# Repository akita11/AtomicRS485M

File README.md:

# Atomic RS485M Base

RS485規格の半二重シリアル通信を行うことができるAtomic Baseです。
M5StackのATOMシリーズを載せて使用します。

[M5Stack社のATOMIC RS485ベース](https://www.switch-science.com/products/9180)とは異なり、本来のRS485の通信仕様でマルチドロップの1:N通信トポロジを構成できます（詳細は後述）。
データを送信している期間のみ伝送路を送信駆動する制御を行うことができます（通信速度は変更可能）。

また伝送路側から最大24Vを供給してマイコン側に5Vを供給することができます。

理論上最大256台まで接続可能な低入力容量型のRS485ドライバを使用しています。

## RS485通信の基本構成と「M5Stack社のATOMIC RS485ベース」との相違点

RS485は、2本の伝送路(Line)を使ってシリアルデータ(UART)を送受信する規格です。
規格の詳細と、M5Stack社のATOMIC RS485ベースでの留意すべき点は[こちら](https://note.com/akita11/n/n0c082069f98c)を参照してください。

「M5Stack社のATOMIC RS485ベース」との相違点は以下です。
（以下のカッコ内の※以下は「M5Stack社のATOMIC RS485ベース」の仕様）

- 非送信時には伝送路が非駆動（※"1"で駆動）
- 送信時のみ伝送路を駆動、1バイト単位自動またはGPIOで制御、自動制御にも設定可能（※常時"1"で駆動）
- 給電入力は48Vまで、24V給電時の過渡応答でも破損しにくい（※給電入力の絶対最大定格が30Vのため24V給電時の過渡応答で破損する場合がある）

## 使い方

基本的には[M5Stack社のATOMIC RS485ベース](https://www.switch-science.com/products/9180)と同じ使い方ですが、送信制御のみ異なり、以下の通りの仕様です。

なおJP5をショートすると伝送路の終端抵抗（120Ω）をONにできます。
またJP6とJP7をショートすると、伝送路のプルアップ・プルダウンを有効にできます（Aプルアップ、Bがプルダウン（5.1kΩ））。

### データ送信

初期設定時には、TXen（ATOM Lite/Matrixの場合はGPIO23）でDriverの有効／無効を制御できます。

1:1接続時の単方向（1つが送信専用、もう1つが受信専用）の場合の送信側は、常時有効（TXen=1）でOKです。

1:N接続時（複数の回路が伝送路Lineにつながる）は、送信デバイスのみがTXen=1としてデータを送信し、その他のデバイスはTXen=0ととすることで、半二重通信が実現されます。

伝送路Receiverは、TXen=1（送信時）のみ無効となりますが、JP8を2-3側に切り替えると、伝送路レシーバReceiverを常時有効に設定できますが、この場合は、自分のDriverが送信したデータを常時受信することになります。

### 伝送路ドライバの自動制御

JP4をショートすると、Driverの自動制御が有効となります。
※このときATOM側のTXen（ATOM Lite/Matrixの場合はGPIO23）は入力設定としてください。

スタートビット検出から1バイト分（10bit分=STARTビット+データ8ビット+STOPビット）の時間だけ自動的にDriverが有効となり、伝送路にデータを送信します（伝送路を駆動中はLEDが点灯）。
このとき、Receiverは無効となり、データを受信しません。
通信方式はN81（8ビット・STOPビット1ビット、パリティなし）で固定です。

データ送信時にDriverを有効とする時間は、データ転送速度（ボーレート）に依存するため、後述の方法で変更できます

### 伝送速度（ボーレート）の変更

ATOM側からBREAK信号（一定時間以上、データ線を"L"に保持）することで、伝送速度変更モードに入り、LEDが点滅します。
この状態で、設定したい伝送速度（ボーレート）で以下のいずれか1バイトを送信することで、その波形から伝送速度を検出し、伝送速度の設定（Driverを有効とする時間）を変更します。
設定された伝送速度は電源を切っても保存されます。

- 'U' (0x55) : 1バイト伝送モード。1バイト伝送終了後の伝送路ドライバがDisableに戻ります。（LEDが3回点滅）
- '5' (0x35) : 連続伝送モード。送信開始語、一定時間データが送られなかった場合に伝送路ドライバがDisableに戻ります。（LEDが5回点滅）

なおBREAK信号は、ATOM等で生成、またはATOM等経由でPC用ターミナルソフトでも送出ができます（TeraTermではAlt+B、MacのscreenコマンドではCtrl+A→Ctr+B）。
[Groveケーブル-USBシリアル接続ケーブル](https://www.switch-science.com/products/9460)などを使って、PCと接続して設定変更や送受信テストができます。

### 電源給電の設定

デフォルトでは、外部からの12/24V給電から本体とATOMへ5Vを供給します。
JP1とJP9で給電方法を変更できます。

- JP9: 給電方法
  - 1-2間: 外部12/24Vから5Vを生成し、本体とATOMへ供給（デフォルト）
  - 2-3間: 外部給電をそのまま本体・ATOMへ接続（※この場合は外部からの給電電圧は5Vとしてください。5V以上の電圧を加えると破損する場合があります）

- JP1: RS485ドライバの電源電圧の変更
  - 1-2間=3.3V（デフォルト）
  - 2-3間=5V

## Author

Junichi Akita (@akita11) / akita@ifdl.jp

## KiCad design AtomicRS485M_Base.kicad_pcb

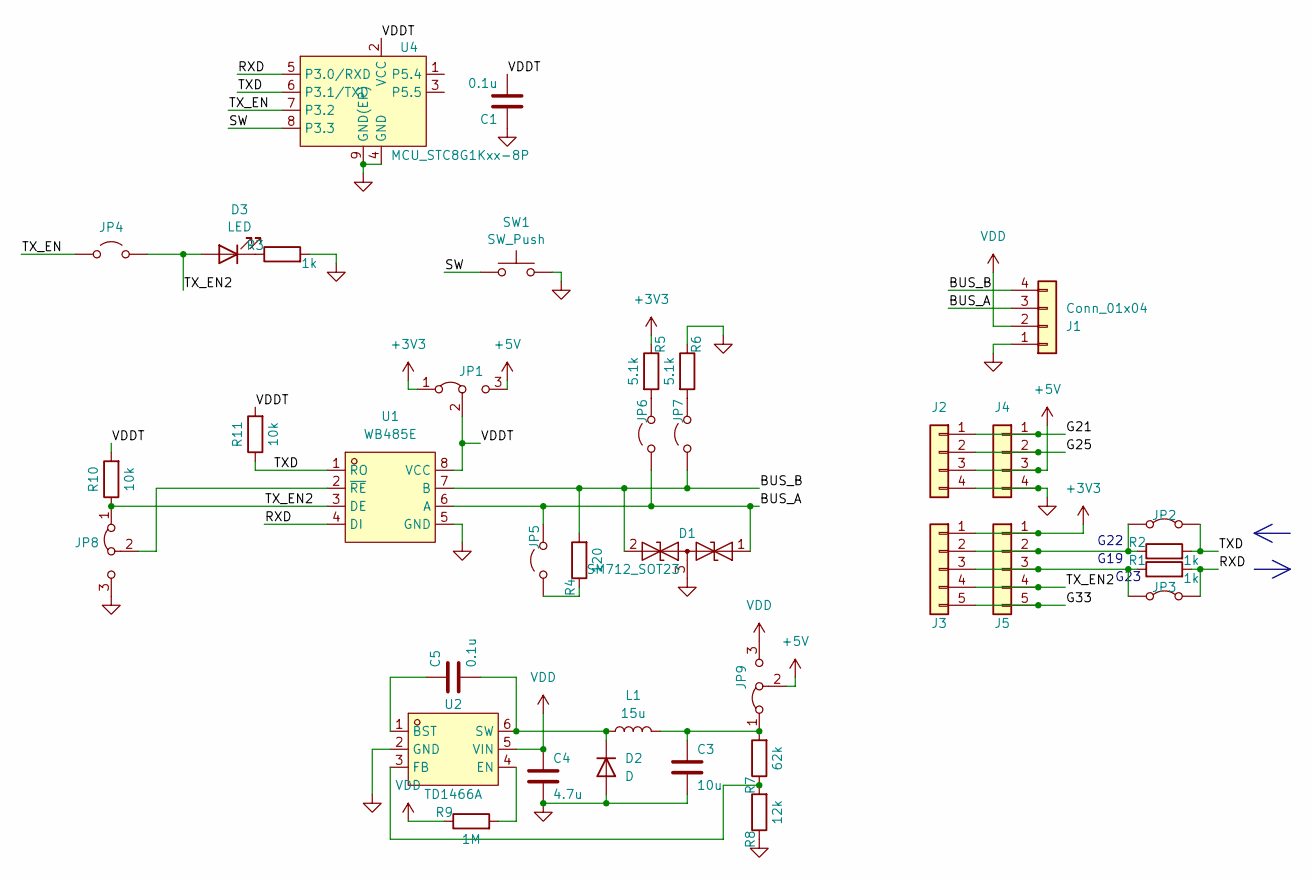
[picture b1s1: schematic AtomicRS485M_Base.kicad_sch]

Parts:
C1, C5: 0.1u; C_0603_1608Metric; LCSC Part C14663
C3: 10u; C_0603_1608Metric; LCSC Part C19702
C4: 4.7u; C_0603_1608Metric; LCSC Part C167655
D1: SM712_SOT23; SOT-23; LCSC Part C5180237
D2: D; D_SOD-123F; LCSC Part C190475
D3: LED; LED_0603_1608Metric; LCSC Part C2286
J1: Conn_01x04; CON_HT396R_4P_hole0.8sq
J2, J4: Conn_01x04; PinHeader_1x04_P2.54mm_Vertical
J3, J5: Conn_01x05; PinHeader_1x05_P2.54mm_Vertical
JP1, JP9: Jumper_3_Bridged12; SolderJumper-3_P1.3mm_Bridged2Bar12_Pad1.0x1.5mm
JP2, JP3: Jumper_2_Bridged; SolderJumper-2_P1.3mm_Bridged_Pad1.0x1.5mm
JP4, JP5, JP6, JP7: Jumper_2_Open; SolderJumper-2_P1.3mm_Open_Pad1.0x1.5mm
JP8: Jumper_3_Bridged12; SolderJumper-3_P1.3mm_Bridged12_Pad1.0x1.5mm
L1: 15u; L_CD43; LCSC Part C5289403
R1, R2, R3: 1k; R_0603_1608Metric; LCSC Part C21190
R4: 120; R_0603_1608Metric; LCSC Part C286567
R5, R6: 5.1k; R_0603_1608Metric; LCSC Part C23186
R7: 62k; R_0603_1608Metric; LCSC Part C3017756
R8: 12k; R_0603_1608Metric; LCSC Part C3017713
R9: 1M; R_0603_1608Metric; LCSC Part C2907115
R10, R11: 10k; R_0603_1608Metric; LCSC C25804
SW1: SW_Push; SW_Push_SPST_NO_Alps_SKRK
U1: WB485E; SOIC-8_L5.0-W4.0-P1.27-LS6.0-BL; LCSC Part C42460582
U2: TD1466A; SOT-23-6_L2.9-W1.7-P0.95-LS2.8-BL; LCSC Part C51928156
U4: MCU_STC8G1Kxx-8P; DFN-8-1EP_3x3mm_P0.5mm_EP1.65x2.38mm; LCSC Part C915664

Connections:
+3V3: J3.1, J5.1, JP1.1 (A), R5.1
+5V: J2.3, J4.3, JP1.3 (B), JP9.2 (C)
/BUS_A: D1.1 (A1), J1.3, JP5.2 (B), JP6.1 (A), U1.6 (A)
/BUS_B: D1.2 (A2), J1.4, JP7.1 (A), R4.2, U1.7 (B)
/G21: J2.1, J4.1
/G25: J2.2, J4.2
/G33: J3.5, J5.5
/RXD: JP3.2 (B), R1.2, U1.4 (DI), U4.5 (P3.0/RXD)
/SW: SW1.1, U4.8 (P3.3)
/TXD: JP2.2 (B), R2.2, R11.1, U1.1 (RO), U4.6 (P3.1/TXD)
/TX_EN: JP4.1 (A), U4.7 (P3.2)
/TX_EN2: D3.2 (A), J3.4, J5.4, JP4.2 (B), JP8.1 (A), R10.1, U1.3 (DE)
/VDDT: C1.2, JP1.2 (C), R10.2, R11.2, U1.8 (VCC), U4.2 (VCC)
GND: C1.1, C3.2, C4.2, D1.3 (common), D2.2 (A), J1.1, J2.4, J4.4, JP8.3 (B), R3.2, R6.1, R8.1, SW1.2, U1.5 (GND), U2.2 (GND), U4.4 (GND), U4.9 (GND(EP))
unnamed: C5.2, D2.1 (K), L1.1, U2.6 (SW)
unnamed: D3.1 (K), R3.1
unnamed: J3.2, J5.2, JP2.1 (A), R2.1
unnamed: J3.3, J5.3, JP3.1 (A), R1.1
unnamed: JP5.1 (A), R4.1
unnamed: JP6.2 (B), R5.2
unnamed: JP7.2 (B), R6.2
unnamed: JP8.2 (C), U1.2 (~RE)
unnamed: C3.1, JP9.1 (A), L1.2, R7.2
unnamed: C5.1, U2.1 (BST)
unnamed: R9.2, U2.4 (EN)
unnamed: R7.1, R8.2, U2.3 (FB)
VDD: C4.1, J1.2, JP9.3 (B), R9.1, U2.5 (VIN)

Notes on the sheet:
G19
G22
G23

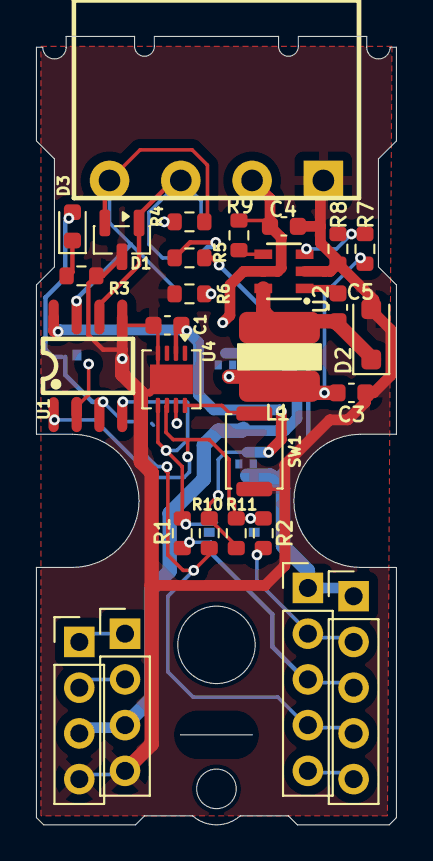
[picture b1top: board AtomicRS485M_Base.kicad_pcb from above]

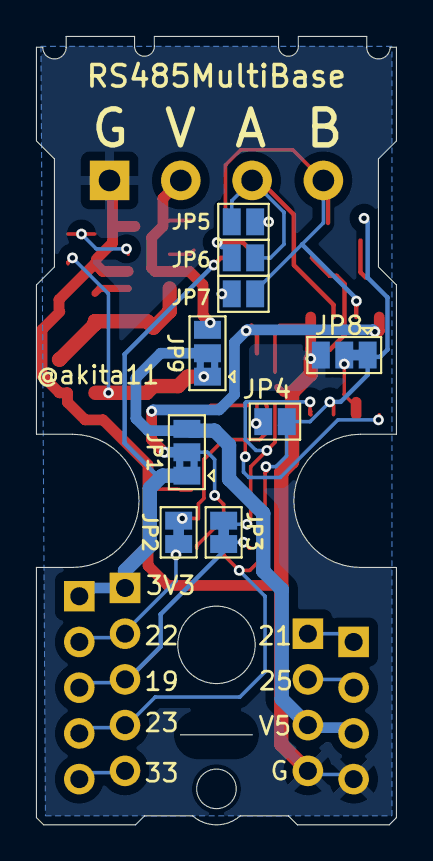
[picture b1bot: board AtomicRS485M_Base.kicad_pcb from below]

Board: 2 copper layers, 20.0 x 43.8 mm, 37 parts (9 on the bottom side), 27 nets.

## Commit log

2026-03-20 update FW
2026-04-01 add photo
